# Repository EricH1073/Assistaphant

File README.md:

**Assistaphant**

A voice and motion controlled digital pet. It is an elephant that can assist with basic tasks.

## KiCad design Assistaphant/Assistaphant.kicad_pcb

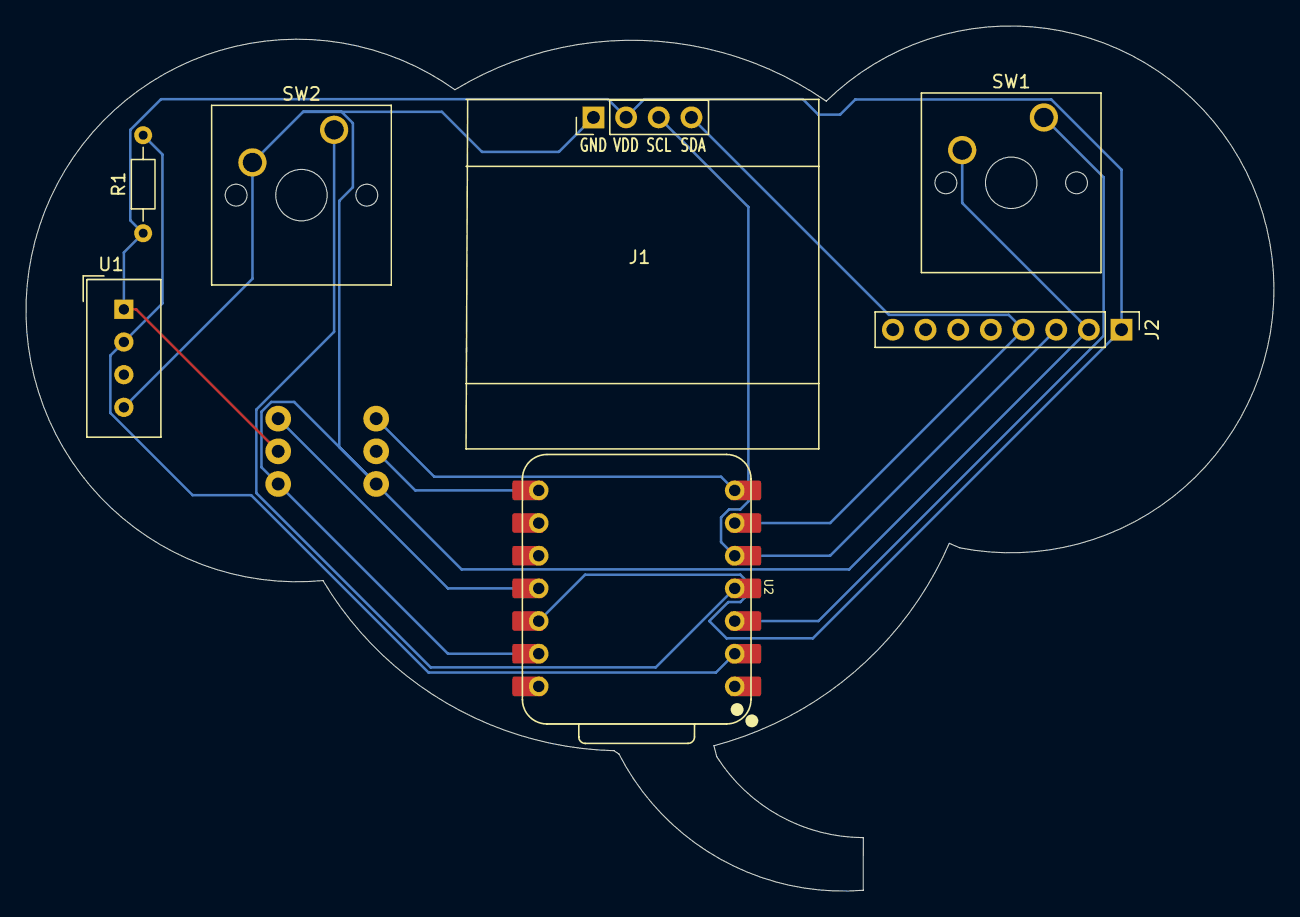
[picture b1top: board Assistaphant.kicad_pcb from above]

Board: 2 copper layers, 97.0 x 67.3 mm, 7 parts (0 on the bottom side), 7 nets.

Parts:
J1: Conn_01x04_Pin; Display_128x64_096_I2C
J2: Conn_01x08_Pin; PinHeader_1x08_P2.54mm_Vertical
R1: 10k; R_Axial_DIN0204_L3.6mm_D1.6mm_P7.62mm_Horizontal
SW1, SW2: SW_Push; SW_Cherry_MX_1.00u_PCB
U1: DHT11; Aosong_DHT11_5.5x12.0_P2.54mm
U2: XIAO-ESP32-C3-SMD; XIAO-ESP32-C6-DIP

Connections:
+3.3V: J1.2, J2.1, R1.1, U1.1 (VDD), U2.12 (3V3_OUT)
/DHT11 DATA: R1.2, U1.2 (DATA), U2.2 (D1)
/GPIO2: SW1.1, U2.3 (D2)
/GPIO3: SW2.1, U2.4 (D3)
/SCL: J1.3, J2.3, U2.5 (D4)
/SDA: J1.4, J2.4, U2.6 (D5)
GND: J1.1, J2.2, SW1.2, SW2.2, U1.4 (GND), U2.13 (GND)
